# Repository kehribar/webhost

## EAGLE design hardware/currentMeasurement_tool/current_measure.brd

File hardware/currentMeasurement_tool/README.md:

Presicion current measurement tool with low burden voltage 
================

This is my attempt to create a battery powered and isolated digital presicion current measurement tool with low burden voltage. Dave L. Jone's uCurrent [http://www.eevblog.com/projects/ucurrent/](http://www.eevblog.com/projects/ucurrent/) board was my inspiration to create this design. 

What I've learned from the uCurrent design is that one way to have a low dropout voltage while maintaining to have a high accuracy when making current measurement is to amplifiy the shunt voltage with a known gain. I've used a application spesific instrumentation amplifier from Analog Devices named AD8293 [http://www.analog.com/static/imported-files/data_sheets/AD8293G80_160.pdf](http://www.analog.com/static/imported-files/data_sheets/AD8293G80_160.pdf). Gain of this amplifier is fixed, which eliminates the need for a high precision resistors.

I've used an 18bit ADC from Microchip named MCP3422. This ADC has its own built-in voltage reference which eliminates the need for an external voltage reference. Lastly, I've used an I2C isolation chip from TI to isolate the battery operated circuit via the I2C host side.

I've ordered parts for this board but haven't populated and tested yet ...

### Schematic

### Layout

### Build

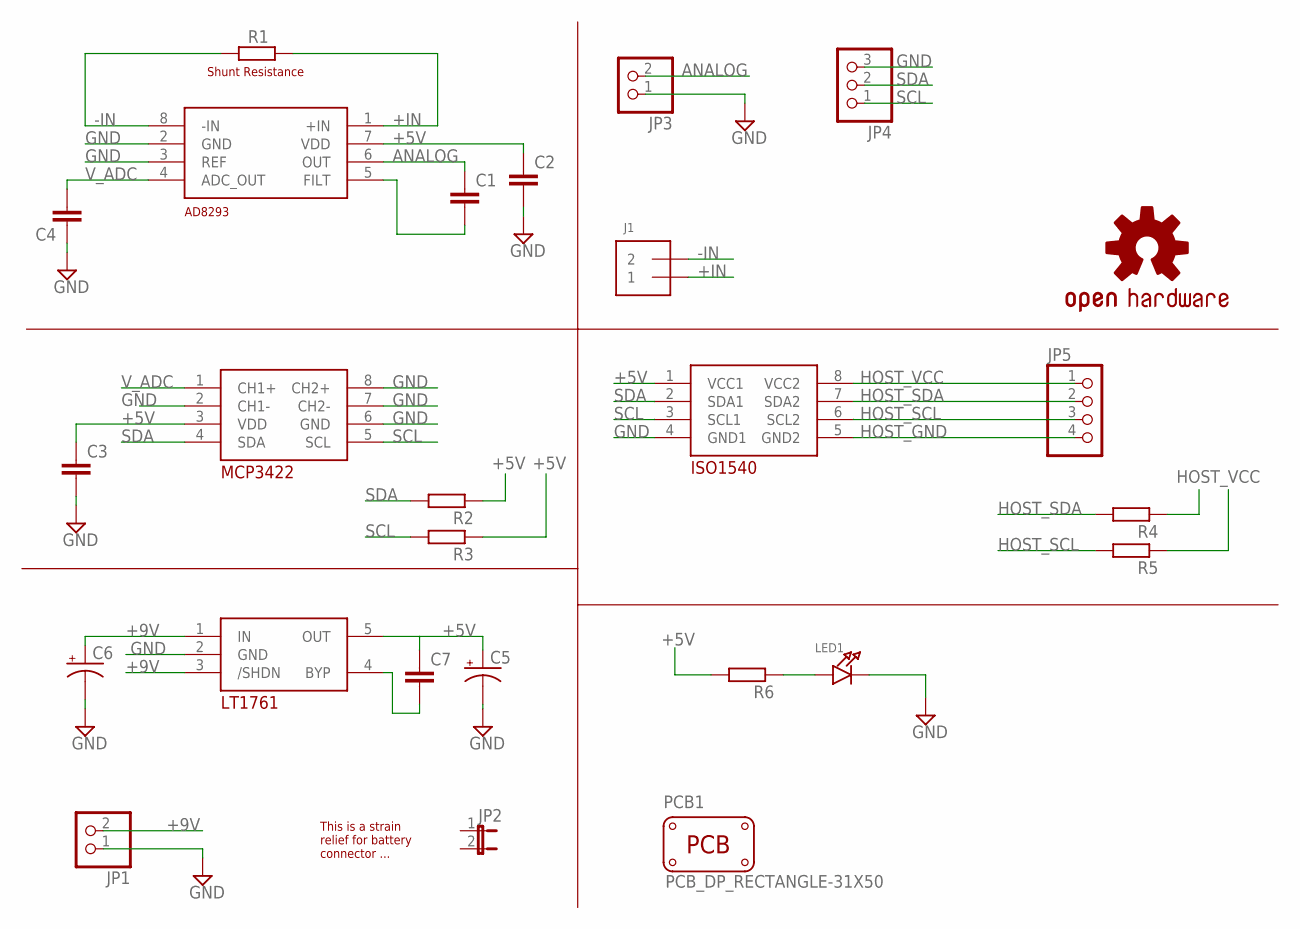
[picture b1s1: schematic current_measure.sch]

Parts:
C1, C2, C3, C4, C7: C-EUC0603; C0603
C5, C6: CPOL-USC/6032-28R; C/6032-28R
J1: TERMBLOCK_1X2; TERMBLOCK_1X2-3.5MM
JP1, JP3: PINHD-1X2; 1X02
JP2: JUMPER2
JP4: HEADER-1X3ROUND; 1X03_ROUND
JP5: HEADER-1X4ROUND; 1X04_ROUND
LED1: LED0805_NOOUTLINE; CHIPLED_0805_NOOUTLINE
LOGO1: OSHW-LOGOM; OSHW-LOGO-M
PCB1: PCB_DP_RECTANGLE-31X50; DP5031_V1
R1: R-EU_R1206; R1206
R2, R3, R4, R5, R6: R-EU_R0603; R0603
U$1: IHSAN_AD8293; SOT23-8
U$2: IHSAN_MCP3422; SO08
U$3: IHSAN_LT1761; SOT23-5
U$4: IHSAN_ISO1540; SO08

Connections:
+5V: C2.1, C3.1, C5.+, C7.1, R2.1, R3.1, R6.2, U$1.7 (VDD), U$2.3 (VDD), U$3.5 (OUT), U$4.1 (VCC1)
+9V: C6.+, JP1.2, U$3.1 (IN), U$3.3 (/SHDN)
+IN: J1.1, R1.2, U$1.1 (+IN)
-IN: J1.2, R1.1, U$1.8 (-IN)
ANALOG: C1.1, JP3.2, U$1.6 (OUT)
GND: C2.2, C3.2, C4.1, C5.-, C6.-, JP1.1, JP3.1, JP4.3, LED1.C, U$1.2 (GND), U$1.3 (REF), U$2.2 (CH1-), U$2.6 (GND), U$2.7 (CH2-), U$2.8 (CH2+), U$3.2 (GND), U$4.4 (GND1)
HOST_GND: JP5.4, U$4.5 (GND2)
HOST_SCL: JP5.3, R5.2, U$4.6 (SCL2)
HOST_SDA: JP5.2, R4.2, U$4.7 (SDA2)
HOST_VCC: JP5.1, R4.1, R5.1, U$4.8 (VCC2)
unnamed: LED1.A, R6.1
unnamed: C7.2, U$3.4 (BYP)
unnamed: C1.2, U$1.5 (FILT)
SCL: JP4.1, R3.2, U$2.5 (SCL), U$4.3 (SCL1)
SDA: JP4.2, R2.2, U$2.4 (SDA), U$4.2 (SDA1)
V_ADC: C4.2, U$1.4 (ADC_OUT), U$2.1 (CH1+)

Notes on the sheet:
Shunt Resistance
This is a strain relief for battery connector ...

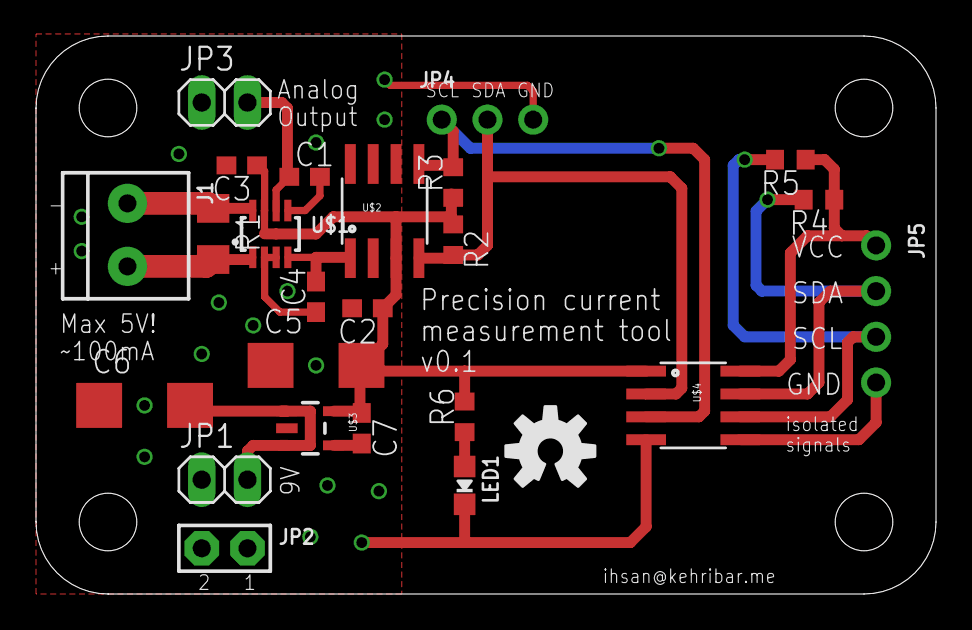
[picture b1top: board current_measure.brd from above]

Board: 2 copper layers, 50.0 x 31.0 mm, 26 parts (0 on the bottom side), 16 nets.

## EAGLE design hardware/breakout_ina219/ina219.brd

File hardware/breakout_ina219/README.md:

INA219 breakout board
================

Simple breakout board for INA219 digital current measurement IC.

### Schematic

### Layout

### Build

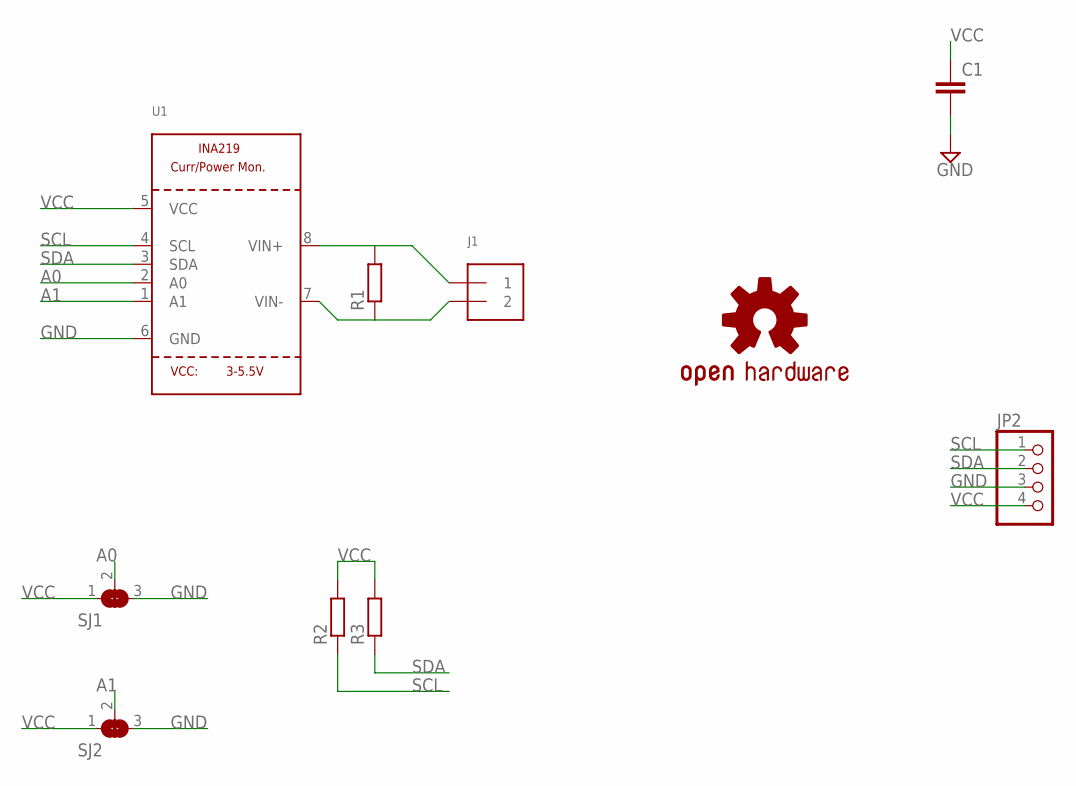
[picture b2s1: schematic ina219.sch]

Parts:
C1: C-EUC0805; C0805
J1: TERMBLOCK_1X2; TERMBLOCK_1X2-3.5MM
JP2: PINHD-1X4; 1X04
LOGO1: OSHW-LOGOS; OSHW-LOGO-S
R1: R-EU_R1206; R1206
R2, R3: R-EU_R0805; R0805
SJ1, SJ2: SOLDERJUMPER_2WAY0603; SOLDERJUMPER_2WAY_OPEN_0603
U1: INA219SOIC8; SOIC8_150MIL

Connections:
A0: SJ1.2, U1.2 (A0)
A1: SJ2.2, U1.1 (A1)
GND: C1.2, JP2.3, SJ1.3, SJ2.3, U1.6 (GND)
unnamed: J1.1, R1.2, U1.8 (VIN+)
unnamed: J1.2, R1.1, U1.7 (VIN-)
SCL: JP2.1, R2.1, U1.4 (SCL)
SDA: JP2.2, R3.1, U1.3 (SDA)
VCC: C1.1, JP2.4, R2.2, R3.2, SJ1.1, SJ2.1, U1.5 (VCC)

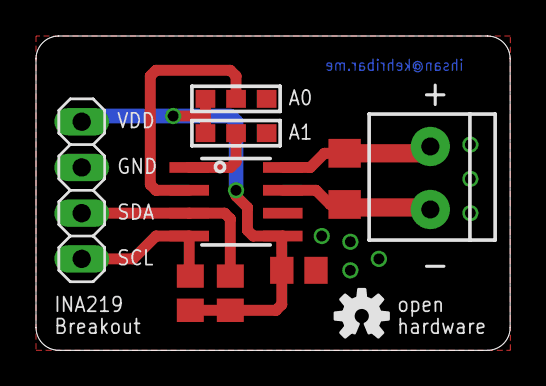
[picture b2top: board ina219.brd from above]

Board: 2 copper layers, 26.3 x 17.5 mm, 10 parts (0 on the bottom side), 8 nets.

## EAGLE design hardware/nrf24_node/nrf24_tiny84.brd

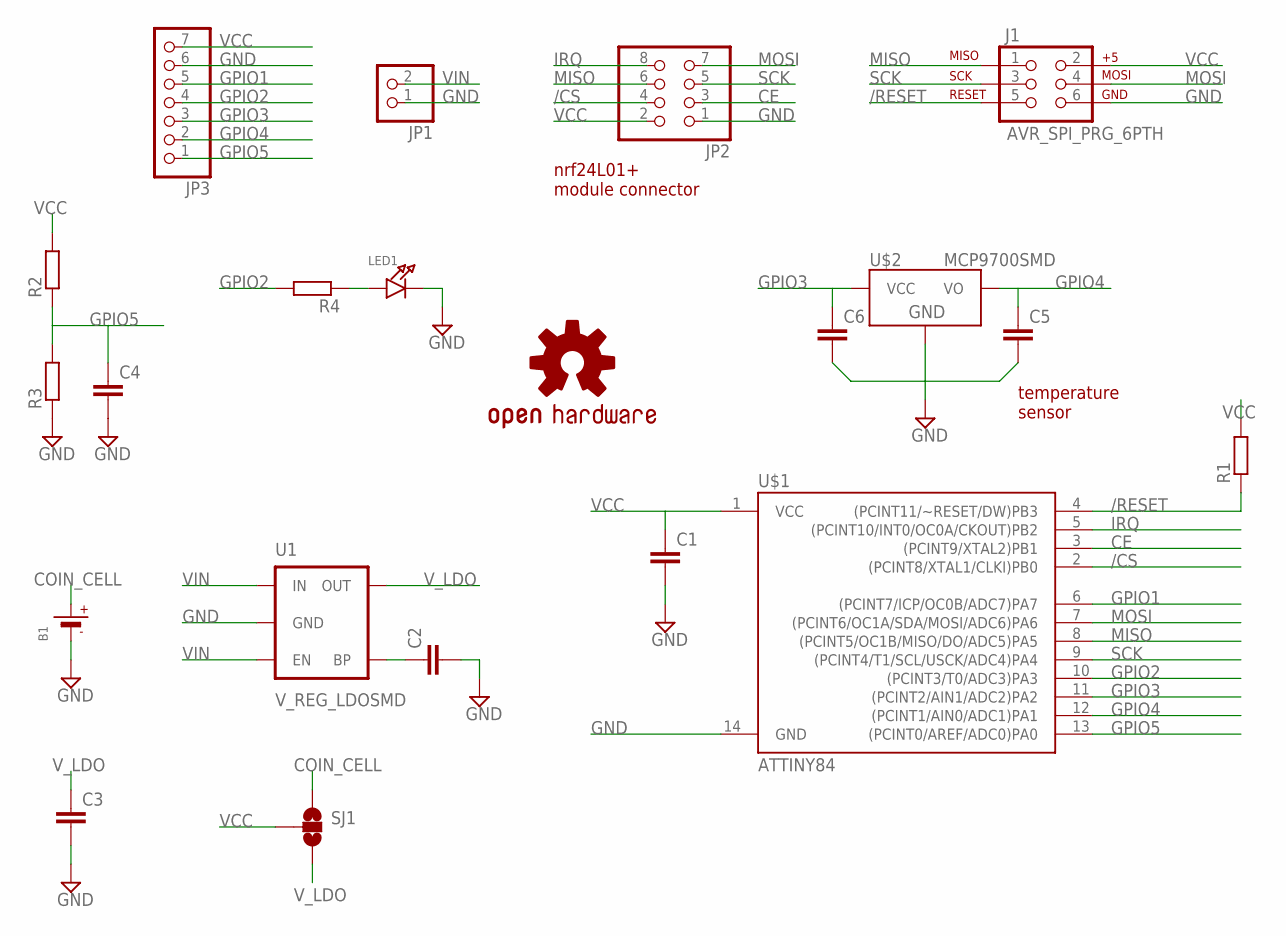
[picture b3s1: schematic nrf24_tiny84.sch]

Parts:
B1: BATTERYCR2032; CR2032
C1, C2, C3, C4, C5, C6: C-EUC0805; C0805
J1: AVR_SPI_PRG_6PTH; 2X3
JP1: HEADER-1X2ROUND; 1X02_ROUND
JP2: PINHD-2X4; 2X04
JP3: HEADER-1X7ROUND; 1X07_ROUND
LED1: LED0805; CHIPLED_0805
LOGO1: OSHW-LOGOS; OSHW-LOGO-S
R1, R2, R3, R4: R-EU_R0805; R0805
SJ1: SOLDERJUMPER_2WAYS; SJ_3
U1: V_REG_LDOSMD; SOT23-5
U$1: ATTINY84; SO14
U$2: MCP9700SMD; SOT23-3

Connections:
/CS: JP2.4, U$1.2 ((PCINT8/XTAL1/CLKI)PB0)
/RESET: J1.5, R1.1, U$1.4 ((PCINT11/~RESET/DW)PB3)
CE: JP2.3, U$1.3 ((PCINT9/XTAL2)PB1)
COIN_CELL: B1.+, SJ1.1
GND: B1.-, C1.2, C2.2, C3.2, C4.2, C5.2, C6.2, J1.6, JP1.1, JP2.1, JP3.6, LED1.C, R3.1, U1.2 (GND), U$1.14 (GND), U$2.3 (GND)
GPIO1: JP3.5, U$1.6 ((PCINT7/ICP/OC0B/ADC7)PA7)
GPIO2: JP3.4, R4.2, U$1.10 ((PCINT3/T0/ADC3)PA3)
GPIO3: C6.1, JP3.3, U$1.11 ((PCINT2/AIN1/ADC2)PA2), U$2.1 (VCC)
GPIO4: C5.1, JP3.2, U$1.12 ((PCINT1/AIN0/ADC1)PA1), U$2.2 (VO)
GPIO5: C4.1, JP3.1, R2.1, R3.2, U$1.13 ((PCINT0/AREF/ADC0)PA0)
IRQ: JP2.8, U$1.5 ((PCINT10/INT0/OC0A/CKOUT)PB2)
MISO: J1.1, JP2.6, U$1.8 ((PCINT5/OC1B/MISO/DO/ADC5)PA5)
MOSI: J1.4, JP2.7, U$1.7 ((PCINT6/OC1A/SDA/MOSI/ADC6)PA6)
unnamed: C2.1, U1.4 (BP)
unnamed: LED1.A, R4.1
SCK: J1.3, JP2.5, U$1.9 ((PCINT4/T1/SCL/USCK/ADC4)PA4)
VCC: C1.1, J1.2, JP2.2, JP3.7, R1.2, R2.2, SJ1.2, U$1.1 (VCC)
VIN: JP1.2, U1.1 (IN), U1.3 (EN)
V_LDO: C3.1, SJ1.3, U1.5 (OUT)

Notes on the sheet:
nrf24L01+ module connector
temperature sensor

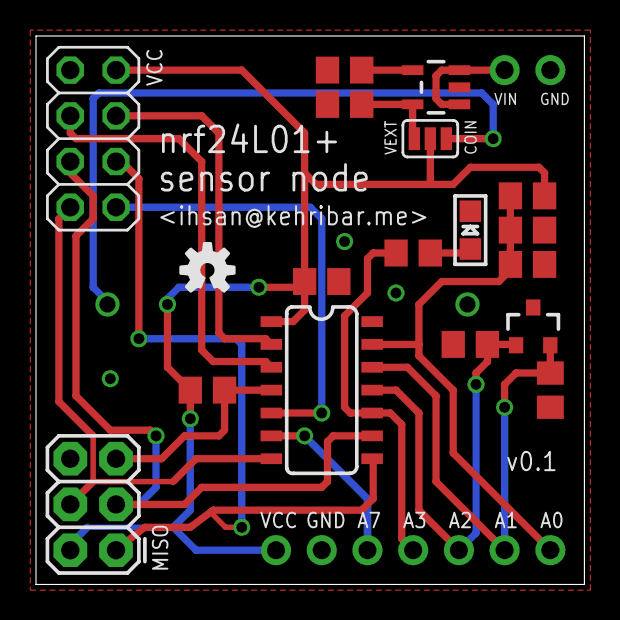
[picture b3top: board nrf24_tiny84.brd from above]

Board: 2 copper layers, 30.5 x 30.5 mm, 21 parts (1 on the bottom side), 19 nets.

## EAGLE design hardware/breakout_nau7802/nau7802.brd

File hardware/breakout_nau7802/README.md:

NAU7802 - 24bit ADC breakout board
================

nau7802 is a great and very affordable 24 bit ADC with reasonable slow sampling rate. The chip itself can be bought at 1.8$ in single quantity from Digikey: [http://www.digikey.com/product-detail/en/NAU7802SGI/NAU7802SGI-ND/2769782](http://www.digikey.com/product-detail/en/NAU7802SGI/NAU7802SGI-ND/2769782) 

I've used and precision 3V voltage reference to drive the ADC's VRef pin. In this configuration, chip can read +/- 1.5V between its differential inputs. Chip outputs the measured value in 2's complement form. Also, even though the chip supports maximum 320 SPS (samples per second), it works best at 10 SPS. Lasty, I've connected the board's VCC into the second channel of the ADC via a voltage divider to measure the VCC voltage. 

I've used this board to precisely measure a voltage which has slow changing rate. I also written a library to use this chip but haven't published it yet.

### Schematic

### Layout

### Build

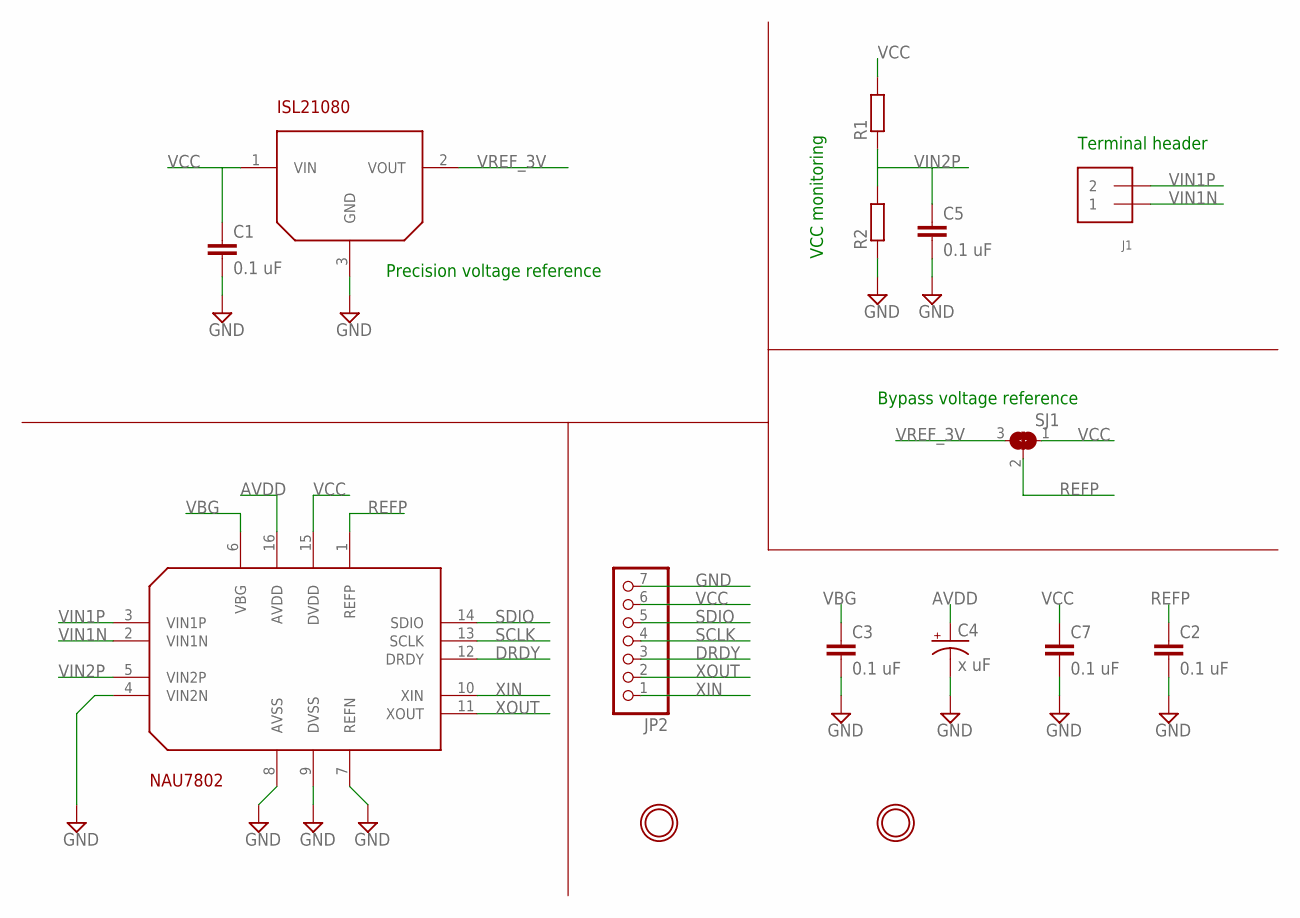
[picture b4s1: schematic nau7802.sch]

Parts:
C1, C2, C3, C5, C7: 0.1 uF; C0805
C4: x uF; D/7343-31W
J1: TERMBLOCK_1X2; TERMBLOCK_1X2-3.5MM
JP2: PINHD-1X7; 1X07
R1, R2: R-EU_R0805; R0805
SJ1: SOLDERJUMPER_2WAY0805; SOLDERJUMPER_2WAY_OPEN_0805
U$1: IHSAN_NAU7802; SO16
U$3: IHSAN_ISL21080; SOT23-3
U$4, U$5: MOUNTINGHOLE3.0THIN; MOUNTINGHOLE_3.0_PLATEDTHIN

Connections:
AVDD: C4.+, U$1.16 (AVDD)
DRDY: JP2.3, U$1.12 (DRDY)
GND: C1.2, C2.2, C3.2, C4.-, C5.2, C7.2, JP2.7, R2.1, U$1.4 (VIN2N), U$1.7 (REFN), U$1.8 (AVSS), U$1.9 (DVSS), U$3.3 (GND)
REFP: C2.1, SJ1.2, U$1.1 (REFP)
SCLK: JP2.4, U$1.13 (SCLK)
SDIO: JP2.5, U$1.14 (SDIO)
VBG: C3.1, U$1.6 (VBG)
VCC: C1.1, C7.1, JP2.6, R1.2, SJ1.1, U$1.15 (DVDD), U$3.1 (VIN)
VIN1N: J1.1, U$1.2 (VIN1N)
VIN1P: J1.2, U$1.3 (VIN1P)
VIN2P: C5.1, R1.1, R2.2, U$1.5 (VIN2P)
VREF_3V: SJ1.3, U$3.2 (VOUT)
XIN: JP2.1, U$1.10 (XIN)
XOUT: JP2.2, U$1.11 (XOUT)

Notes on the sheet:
Precision voltage reference
Terminal header
VCC monitoring
Bypass voltage reference

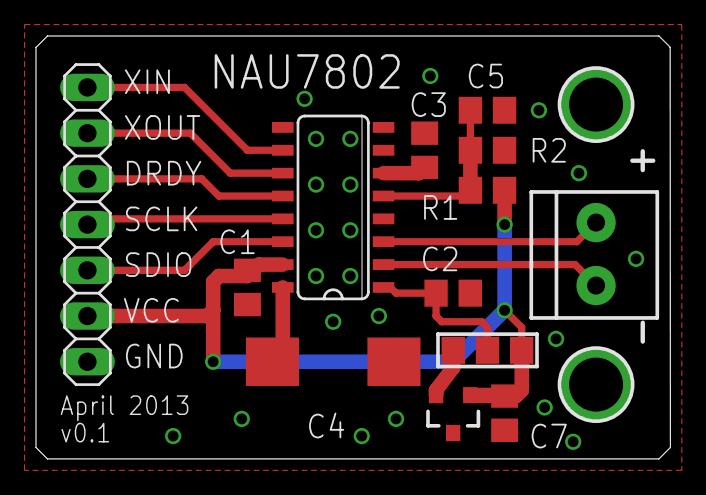
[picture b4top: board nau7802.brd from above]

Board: 2 copper layers, 35.2 x 23.5 mm, 15 parts (0 on the bottom side), 14 nets.

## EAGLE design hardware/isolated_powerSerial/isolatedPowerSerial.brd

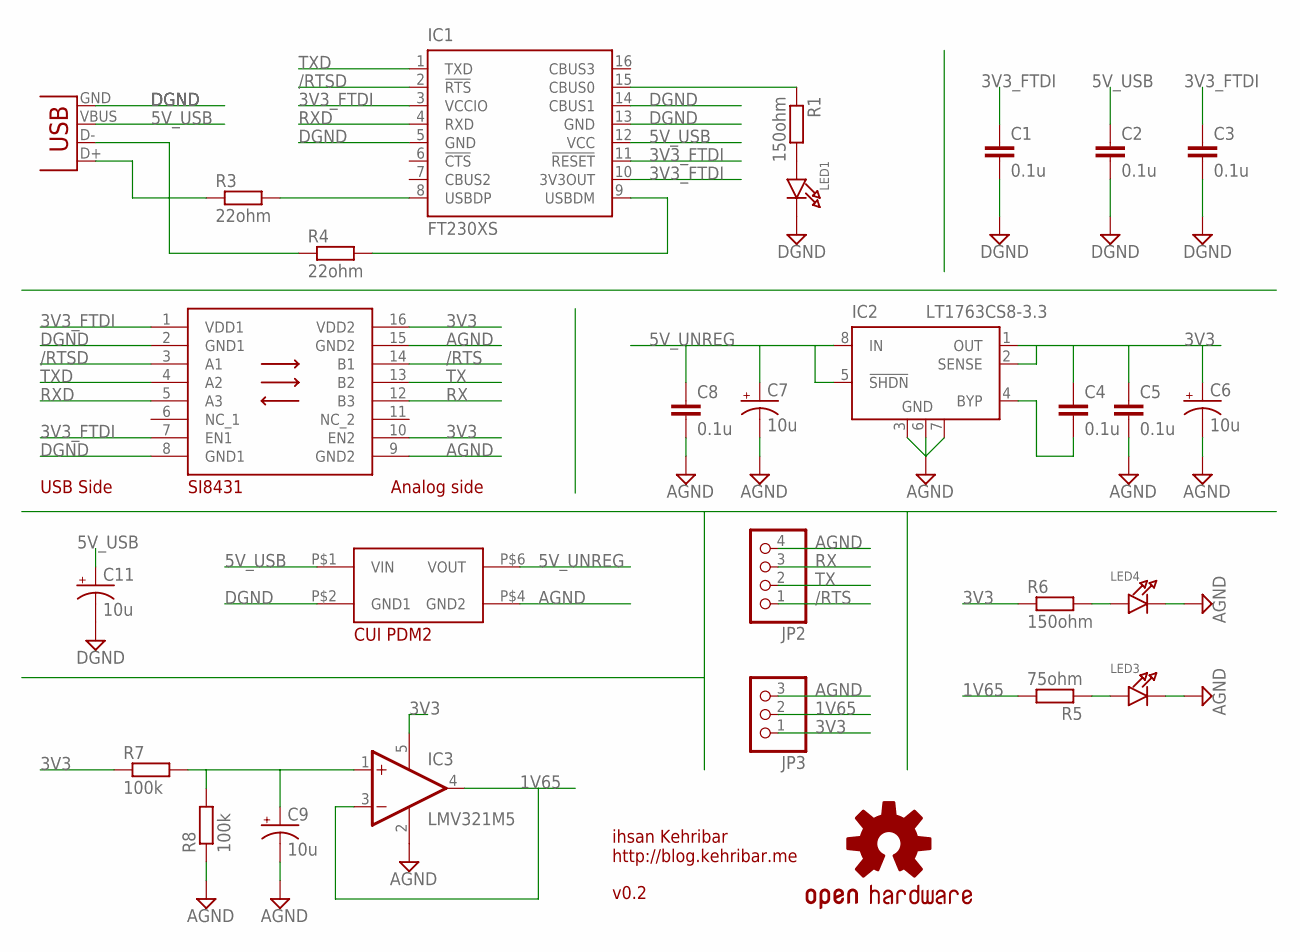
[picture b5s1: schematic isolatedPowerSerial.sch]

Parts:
C1, C2, C3, C4, C5, C8: 0.1u; C0805
C6, C7, C9, C11: 10u; B/3528-21R
IC1: FT230XS; SSOP16
IC2: LT1763CS8-3.3; SOIC8
IC3: LMV321M5; SOT23-5
JP1: USBSMD; USB-MINIB
JP2: HEADER-1X4ROUND; 1X04_ROUND
JP3: HEADER-1X3ROUND; 1X03_ROUND
LED1, LED3, LED4: LED0805; CHIPLED_0805
LOGO1: OSHW-LOGOS; OSHW-LOGO-S
R1, R6: 150ohm; R0805
R3, R4: 22ohm; R0805
R5: 75ohm; R0805
R7, R8: 100k; R0805
U$1: IHSAN_SI8431; SO16L
U$2: IHSAN_CUI_PDM2; SIL7

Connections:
1V65: IC3.3 (-IN), IC3.4 (OUT), JP3.2, R5.2
3V3: C4.1, C5.1, C6.+, IC2.1 (OUT), IC2.2 (SENSE), IC3.5 (V+), JP3.1, R6.1, R7.1, U$1.10 (EN2), U$1.16 (VDD2)
3V3_FTDI: C1.1, C3.1, IC1.3 (VCCIO), IC1.10 (3V3OUT), IC1.11 (!RESET), U$1.1 (VDD1), U$1.7 (EN1)
5V_UNREG: C7.+, C8.1, IC2.5 (!SHDN), IC2.8 (IN), U$2.P$6 (VOUT)
5V_USB: C2.1, C11.+, IC1.12 (VCC), JP1.VBUS, U$2.P$1 (VIN)
/RTS: JP2.1, U$1.14 (B1)
/RTSD: IC1.2 (!RTS), U$1.3 (A1)
AGND: C5.2, C6.-, C7.-, C8.2, C9.-, IC2.3 (GND), IC2.6 (GND), IC2.7 (GND), IC3.2 (V-), JP2.4, JP3.3, LED3.C, LED4.C, R8.1, U$1.9 (GND2), U$1.15 (GND2), U$2.P$4 (GND2)
DGND: C1.2, C2.2, C3.2, C11.-, IC1.5 (GND), IC1.13 (GND), IC1.14 (CBUS1), JP1.GND, LED1.C, U$1.2 (GND1), U$1.8 (GND1), U$2.P$2 (GND1)
unnamed: IC1.15 (CBUS0), R1.1
unnamed: IC1.8 (USBDP), R3.2
unnamed: JP1.D+, R3.1
unnamed: JP1.D-, R4.1
unnamed: IC1.9 (USBDM), R4.2
unnamed: C4.2, IC2.4 (BYP)
unnamed: LED3.A, R5.1
unnamed: LED4.A, R6.2
unnamed: LED1.A, R1.2
unnamed: C9.+, IC3.1 (+IN), R7.2, R8.2
RX: JP2.3, U$1.12 (B3)
RXD: IC1.4 (RXD), U$1.5 (A3)
TX: JP2.2, U$1.13 (B2)
TXD: IC1.1 (TXD), U$1.4 (A2)

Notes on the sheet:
USB Side
Analog side
ihsan Kehribar http://blog.kehribar.me
v0.2

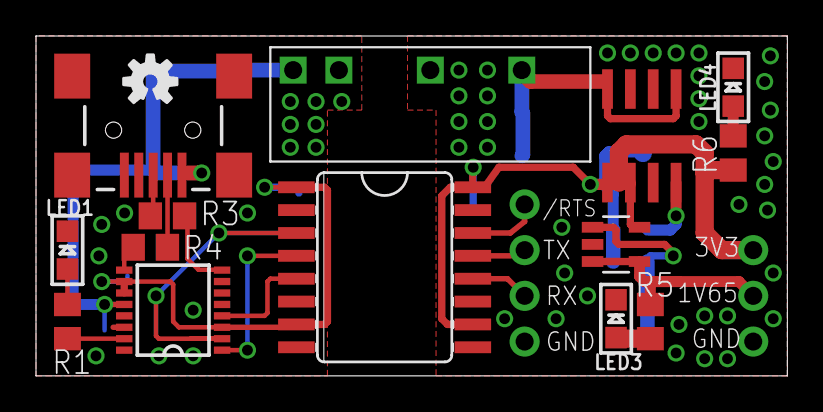
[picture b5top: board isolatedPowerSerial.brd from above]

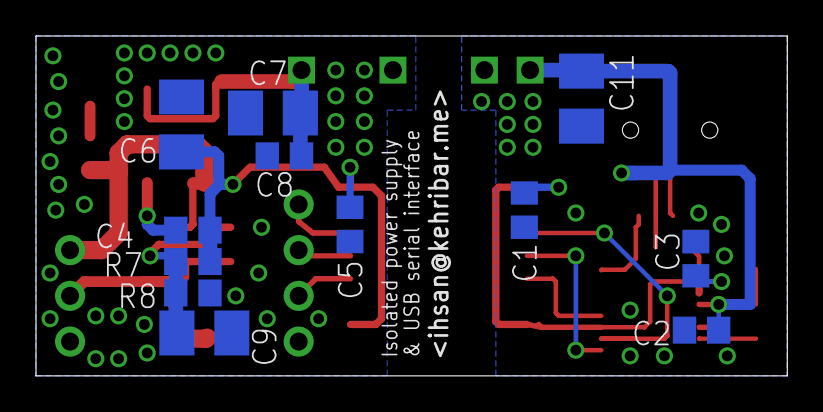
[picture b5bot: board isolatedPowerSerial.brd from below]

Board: 2 copper layers, 41.7 x 18.9 mm, 29 parts (12 on the bottom side), 23 nets.

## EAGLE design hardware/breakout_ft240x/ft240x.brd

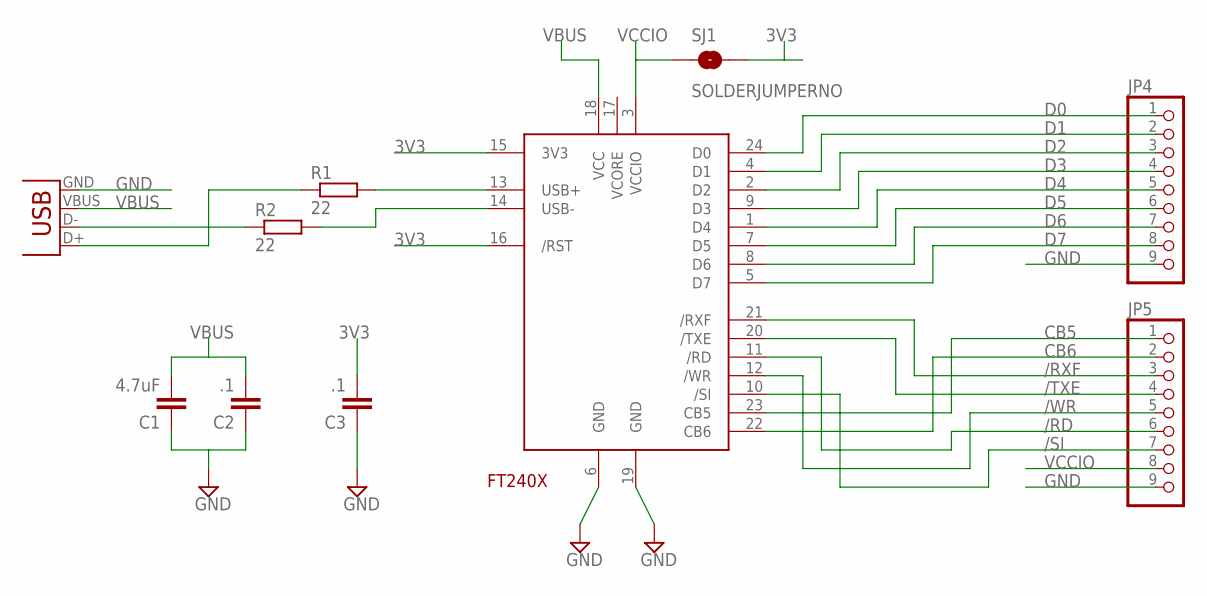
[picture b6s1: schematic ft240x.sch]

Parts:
C1: 4.7uF; C0603
C2, C3: .1; C0603
JP3: USBSMD; USB-MINIB
JP4, JP5: HEADER-1X970MIL; 1X09_ROUND_70
R1, R2: 22; R0603
SJ1: SOLDERJUMPERNO; SJ_2S-NO
U$1: IHSAN_FT240X; SSOP24

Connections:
3V3: C3.2, SJ1.2, U$1.15 (3V3), U$1.16 (/RST)
/RD: JP5.6, U$1.11 (/RD)
/RXF: JP5.3, U$1.21 (/RXF)
/SI: JP5.7, U$1.10 (/SI)
/TXE: JP5.4, U$1.20 (/TXE)
/WR: JP5.5, U$1.12 (/WR)
CB5: JP5.1, U$1.23 (CB5)
CB6: JP5.2, U$1.22 (CB6)
D0: JP4.1, U$1.24 (D0)
D1: JP4.2, U$1.4 (D1)
D2: JP4.3, U$1.2 (D2)
D3: JP4.4, U$1.9 (D3)
D4: JP4.5, U$1.1 (D4)
D5: JP4.6, U$1.7 (D5)
D6: JP4.7, U$1.8 (D6)
D7: JP4.8, U$1.5 (D7)
GND: C1.1, C2.1, C3.1, JP3.GND, JP4.9, JP5.9, U$1.6 (GND), U$1.19 (GND)
unnamed: R1.2, U$1.13 (USB+)
unnamed: R2.2, U$1.14 (USB-)
unnamed: JP3.D+, R1.1
unnamed: JP3.D-, R2.1
VBUS: C1.2, C2.2, JP3.VBUS, U$1.18 (VCC)
VCCIO: JP5.8, SJ1.1, U$1.3 (VCCIO)

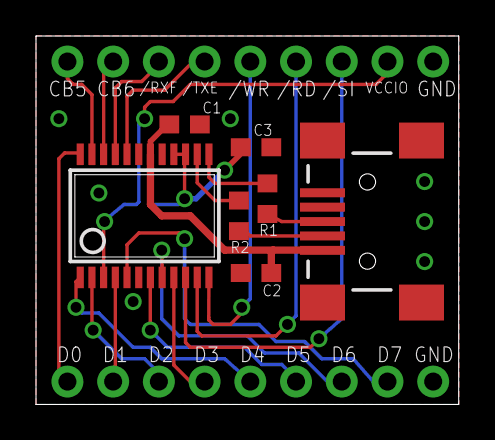
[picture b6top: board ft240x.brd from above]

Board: 2 copper layers, 23.5 x 20.5 mm, 10 parts (1 on the bottom side), 23 nets.

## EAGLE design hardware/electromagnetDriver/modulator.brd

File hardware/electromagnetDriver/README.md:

Intelligent electromagnet driver
================

During my senior year at the college, me and my teammates were working on a Human-Computer Interaction technology called [MagiTact](https://www.google.com/search?btnG=1&pws=0&q=Magitact) for our senior project. In this technology, a permanent magnet is used to manipulate the electromagnetic field arround a mobile device which then interfaces with the internal compass(magnetometer) of the device. By analysing this additional magnetic field, user interaction can be created between the user and the mobile device.

In our study, we created an electromagnet module which can modulates its output power in a spesific frequency. Our aim was to have a multi user interaction with a single magnetometer by demodulating the effects of different magnets in different frequencies at the host side.

This board has an opamp+transistor based constant current source to drive the electromagnet coil. Also there is a quad-mosfet based H-bridge circuit to be able to change the direction of the current flowing in the electromagnet. Sine wave is generated via an I2C based 12bit DAC. The output frequency of this bord can be changed over USB via CDC based serial interface. PIC18F13K50 microcontroller is used as the main controller. There is also a charging circuitry for LiPo batteries when the device is connected to the USB.

Routing for this circuit is all done by myself. After routing, this board is manufactured via a LPKF milling machine available at my university then silkscreen is applied to the board manually with additional LPKF tools. 

### Schematic

### Layout

### Build

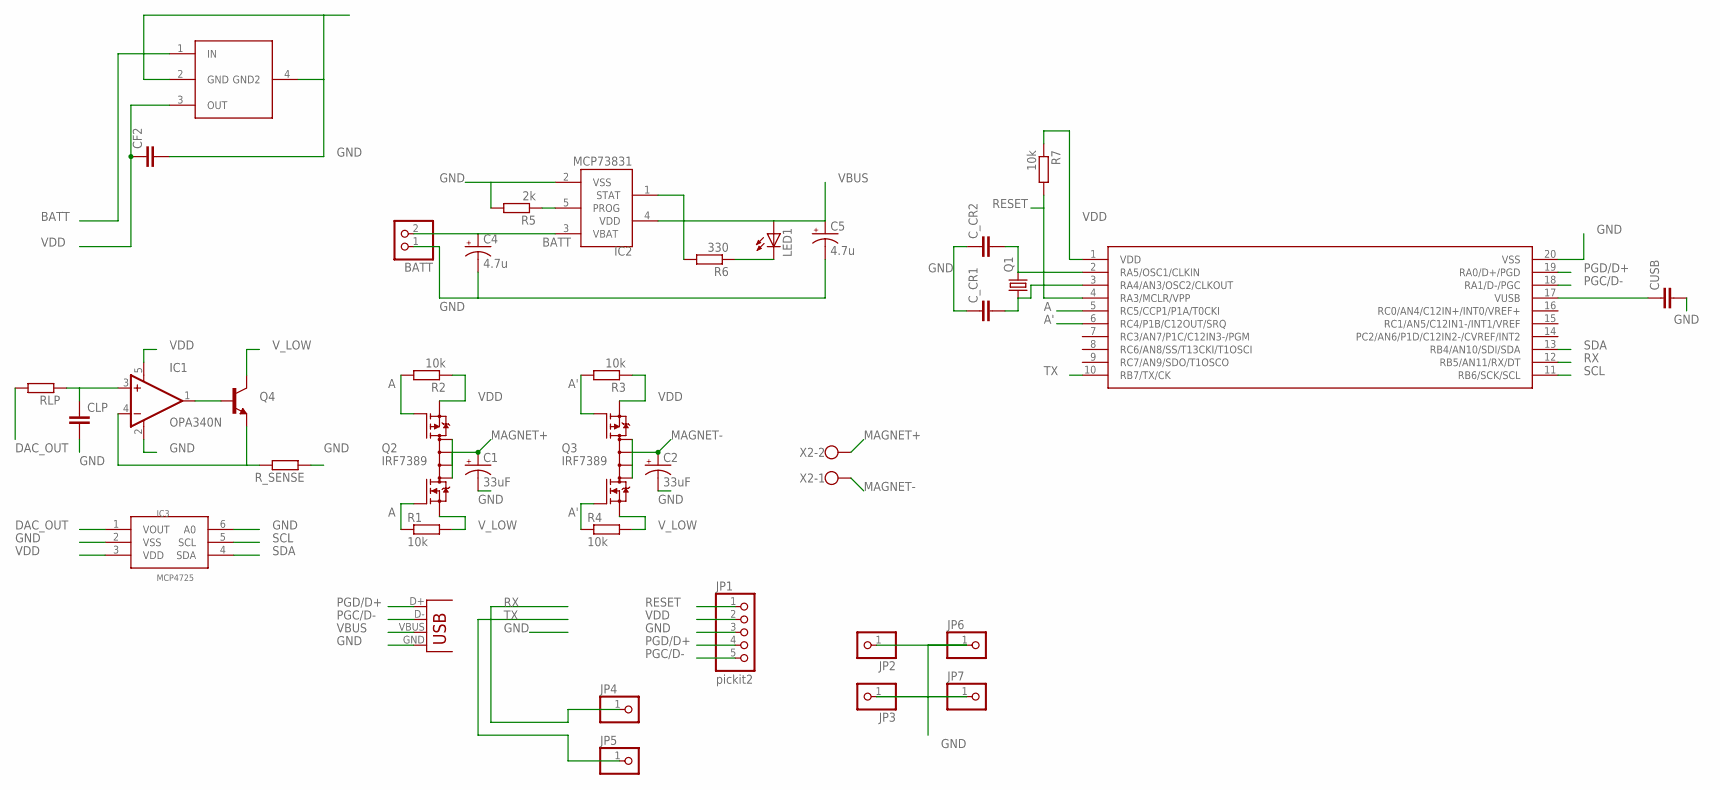
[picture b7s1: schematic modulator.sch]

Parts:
BATT: PINHD-1X2; 1X02
C1, C2: 33uF; B/3528-21W
C4, C5: 4.7u; B/3528-21W
CF2: C-EUC1206; C1206
CLP: C-EUC1206; C1206
CUSB: C-EUC1206; C1206
C_CR1, C_CR2: C-EUC1206; C1206
IC1: OPA340N; SOT23-5
IC2: MCP73831; SOT23-5L
IC3: MCP4725; SOT23-6
JP1: pickit2; 1X05
JP2, JP3, JP4, JP5, JP6, JP7: PINHD-1X1; 1X01
LED1: LED1206; LED-1206
Q1: CRYSTAL5X3; CRYSTAL-SMD-5X3
Q2, Q3: IRF7389; SO08-IRF
Q4: TRANSISTOR_NPNSOT23; SOT23
R1, R2, R3, R4, R7: 10k; R1206W
R5: 2k; R1206W
R6: 330; R1206W
RLP: R-EU_R1206W; R1206W
R_SENSE: R-EU_R1206W; R1206W
U$1: PIC18F4X; SSOP20
U$3: MCP1826S; SOT223
X1: USB-SMD-NS; USB-MINIB-NOSTOP
X2: W237-102

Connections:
A: Q2.2 (N-G), Q2.4 (P-G), R1.1, R2.2, U$1.5 (RC5/CCP1/P1A/T0CKI)
A': Q3.2 (N-G), Q3.4 (P-G), R3.2, R4.1, U$1.6 (RC4/P1B/C12OUT/SRQ)
BATT: BATT.2, C4.+, IC2.3 (VBAT), U$3.1 (IN)
DAC_OUT: IC3.1 (VOUT), RLP.2
GND: BATT.1, C1.-, C2.-, C4.-, C5.-, CF2.2, CLP.2, CUSB.2, C_CR1.1, C_CR2.1, IC1.2 (V-), IC2.2 (VSS), IC3.2 (VSS), IC3.6 (A0), JP1.3, JP2.1, JP3.1, JP6.1, JP7.1, R5.2, R_SENSE.1, U$1.20 (VSS), U$3.2 (GND), U$3.4 (GND2), X1.GND
MAGNET+: C1.+, Q2.5 (D), Q2.6 (D), Q2.7 (D), Q2.8 (D), X2.2
MAGNET-: C2.+, Q3.5 (D), Q3.6 (D), Q3.7 (D), Q3.8 (D), X2.1
unnamed: IC1.1 (OUT), Q4.1 (B)
unnamed: IC1.4 (-IN), Q4.2 (E), R_SENSE.2
unnamed: CLP.1, IC1.3 (+IN), RLP.1
unnamed: CUSB.1, U$1.17 (VUSB)
unnamed: IC2.5 (PROG), R5.1
unnamed: C_CR1.2, Q1.1, U$1.3 (RA4/AN3/OSC2/CLKOUT)
unnamed: C_CR2.2, Q1.3 (2), U$1.2 (RA5/OSC1/CLKIN)
unnamed: LED1.C, R6.1
unnamed: IC2.1 (STAT), R6.2
PGC/D-: JP1.5, U$1.18 (RA1/D-/PGC), X1.D-
PGD/D+: JP1.4, U$1.19 (RA0/D+/PGD), X1.D+
RESET: JP1.1, R7.2, U$1.4 (RA3/MCLR/VPP)
RX: JP4.1, U$1.12 (RB5/AN11/RX/DT)
SCL: IC3.5 (SCL), U$1.11 (RB6/SCK/SCL)
SDA: IC3.4 (SDA), U$1.13 (RB4/AN10/SDI/SDA)
TX: JP5.1, U$1.10 (RB7/TX/CK)
VBUS: C5.+, IC2.4 (VDD), LED1.A, X1.VBUS
VDD: CF2.1, IC1.5 (V+), IC3.3 (VDD), JP1.2, Q2.3 (P-S), Q3.3 (P-S), R2.1, R3.1, R7.1, U$1.1 (VDD), U$3.3 (OUT)
V_LOW: Q2.1 (N-S), Q3.1 (N-S), Q4.3 (C), R1.2, R4.2

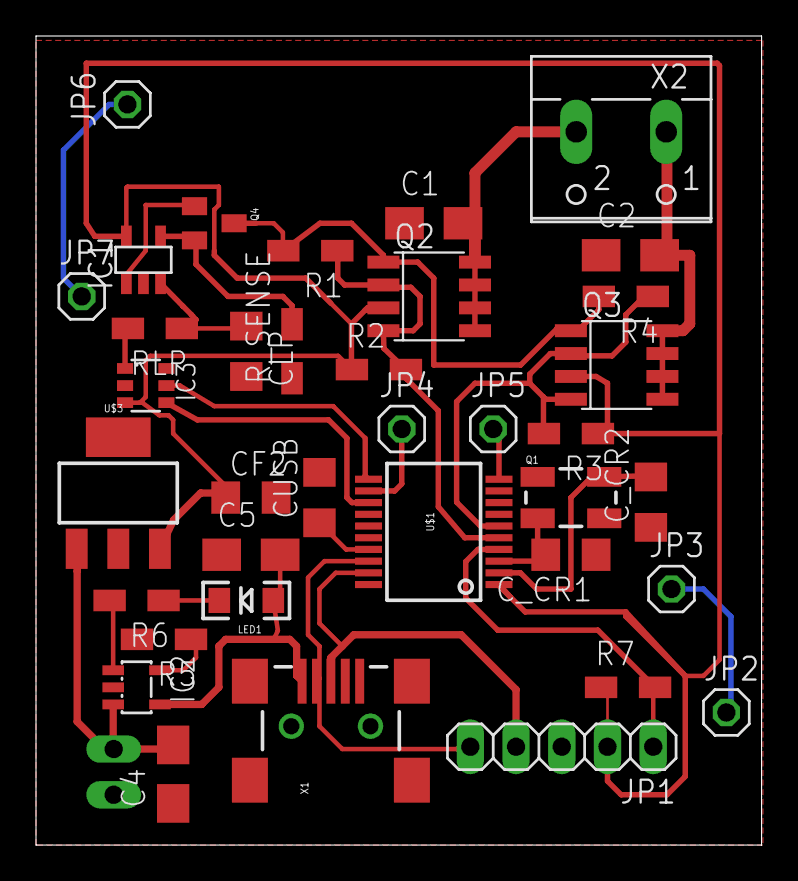
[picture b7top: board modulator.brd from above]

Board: 2 copper layers, 40.3 x 44.9 mm, 38 parts (1 on the bottom side), 26 nets.

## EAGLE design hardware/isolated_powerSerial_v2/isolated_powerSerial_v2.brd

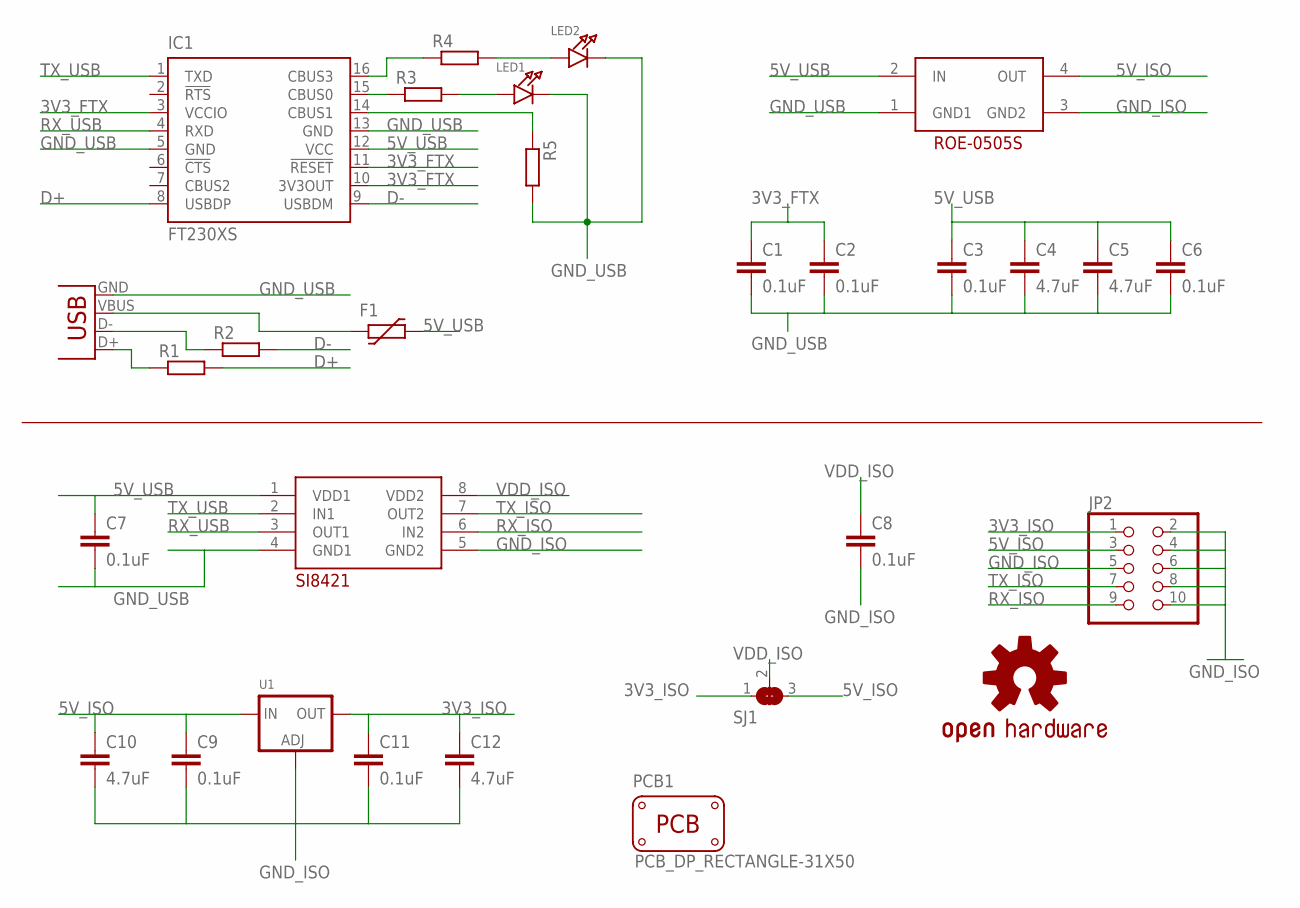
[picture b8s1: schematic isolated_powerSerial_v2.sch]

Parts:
C1, C2, C3, C6, C7, C8, C9, C11: 0.1uF; C0603
C4, C5, C10, C12: 4.7uF; C0603
F1: FUSE_PTC-0805; PTC0805
IC1: FT230XS; SSOP16
JP1: USB-SMD-NS; USB-MINIB-NOSTOP
JP2: PINHD-2X5; 2X05
LED1, LED2: LED0805; CHIPLED_0805
LOGO1: OSHW-LOGOS; OSHW-LOGO-S
PCB1: PCB_DP_RECTANGLE-31X50; DP5031_V1
R1, R2, R3, R4, R5: R-EU_R0603; R0603
SJ1: SOLDERJUMPER_2WAY0603; SOLDERJUMPER_2WAY_OPEN_0603
U1: LM1117SOT223-REFLOW; SOT223-R
U$1: IHSAN_RECOM_ROE-0505S; IHSAN_ROE
U$2: IHSAN_SI8421; SO08

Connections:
3V3_FTX: C1.1, C2.1, IC1.3 (VCCIO), IC1.10 (3V3OUT), IC1.11 (!RESET)
3V3_ISO: C11.1, C12.1, JP2.1, SJ1.1, U1.2 (OUT)
5V_ISO: C9.1, C10.1, JP2.3, SJ1.3, U1.3 (IN), U$1.4 (OUT)
5V_USB: C3.1, C4.1, C5.1, C6.1, C7.1, F1.2, IC1.12 (VCC), U$1.2 (IN), U$2.1 (VDD1)
D+: IC1.8 (USBDP), R1.2
D-: IC1.9 (USBDM), R2.2
GND_ISO: C8.2, C9.2, C10.2, C11.2, C12.2, JP2.2, JP2.4, JP2.5, JP2.6, JP2.8, JP2.10, U1.1 (ADJ), U$1.3 (GND2), U$2.5 (GND2)
GND_USB: C1.2, C2.2, C3.2, C4.2, C5.2, C6.2, C7.2, IC1.5 (GND), IC1.13 (GND), JP1.GND, LED1.C, LED2.C, R5.2, U$1.1 (GND1), U$2.4 (GND1)
unnamed: JP1.D-, R2.1
unnamed: JP1.D+, R1.1
unnamed: LED1.A, R3.2
unnamed: LED2.A, R4.2
unnamed: F1.1, JP1.VBUS
unnamed: IC1.14 (CBUS1), R5.1
unnamed: IC1.15 (CBUS0), R3.1
unnamed: IC1.16 (CBUS3), R4.1
RX_ISO: JP2.9, U$2.6 (IN2)
RX_USB: IC1.4 (RXD), U$2.3 (OUT1)
TX_ISO: JP2.7, U$2.7 (OUT2)
TX_USB: IC1.1 (TXD), U$2.2 (IN1)
VDD_ISO: C8.1, SJ1.2, U$2.8 (VDD2)

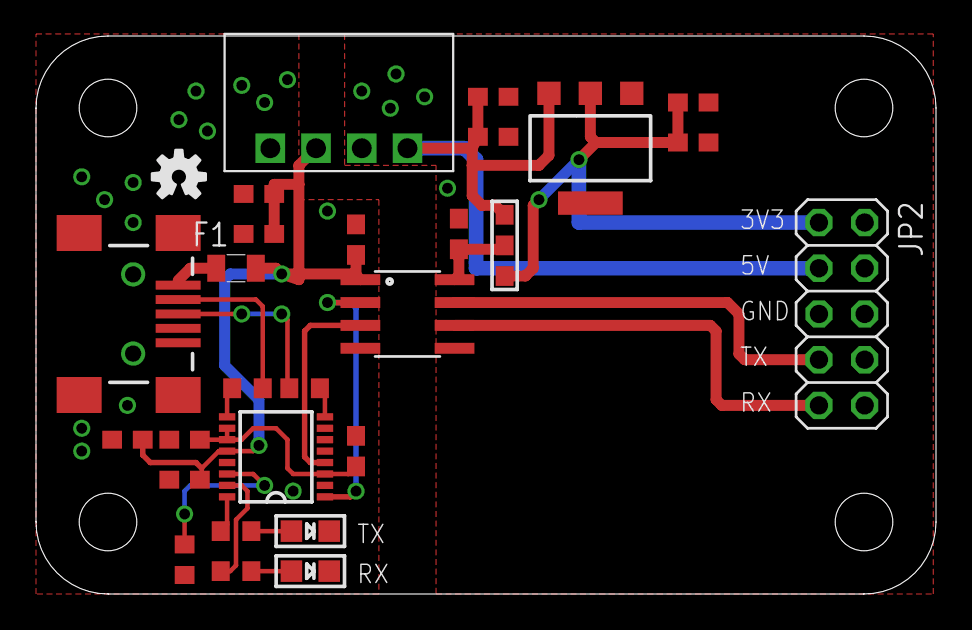
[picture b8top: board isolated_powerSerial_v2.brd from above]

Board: 2 copper layers, 50.0 x 31.0 mm, 29 parts (0 on the bottom side), 21 nets.

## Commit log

2016-09-05 Dump the old web page content.
2016-09-05 Added some filler text to fit the page layout better
2016-09-05 Files moved to different branch.
2016-09-05 add domain information

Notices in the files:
parts and their libraries:
SparkFun-DigitalIC_ihsan: Licensing: CC v3.0 Share-Alike You are welcome to use this library for commercial purposes.
microbuilder: This work is placed in the public domain, and may be freely used for commercial and non-commercial work with the following conditions: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
